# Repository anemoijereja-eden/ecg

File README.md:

E.D.E.N.Tech Open Source Hardware health telemetry system
This project aims to bring the features of medical grade wireless telemetry systems to the people, making them vastly more compact and lowering costs significantly.
Where the average medical grade device that does what this unit can costs hundreds of dollars and only supports proprietary EMR systems, this device uses commodity parts and is intended to connect to an open source telemetry system based on InfluxDB.

Current work completed:
- Signal acquisition using an esp32-s3
- Off device signal processing
- first revision PCB design

To Do:
- Move signal processing onto the device itself
- enable device to report data over the network
- finish PCB designs and create the actual device
- create software solution for processing telemetry data on a recieving server
- Look into other telemetry to integrate

Potential ideas:
- non-invasive blood pressure monitor built more compact than ever before using a PCB motor, integrated cycloidal drive, and a membrane pump to create the full system at a pcb scale.
- integration with implanted sensors via nfc

Tech Stack:
The system is based around the AD8232 as an analog frontend, connected to an ESP32-S3 microcontroller to create a low cost platform using parts that are already widely used and accepted in open hardware.
This repository contains an esp32 firmware, a kicad project under the "PCB" subdirectory, and the prototype off-device processing scripts in "plotter.py"

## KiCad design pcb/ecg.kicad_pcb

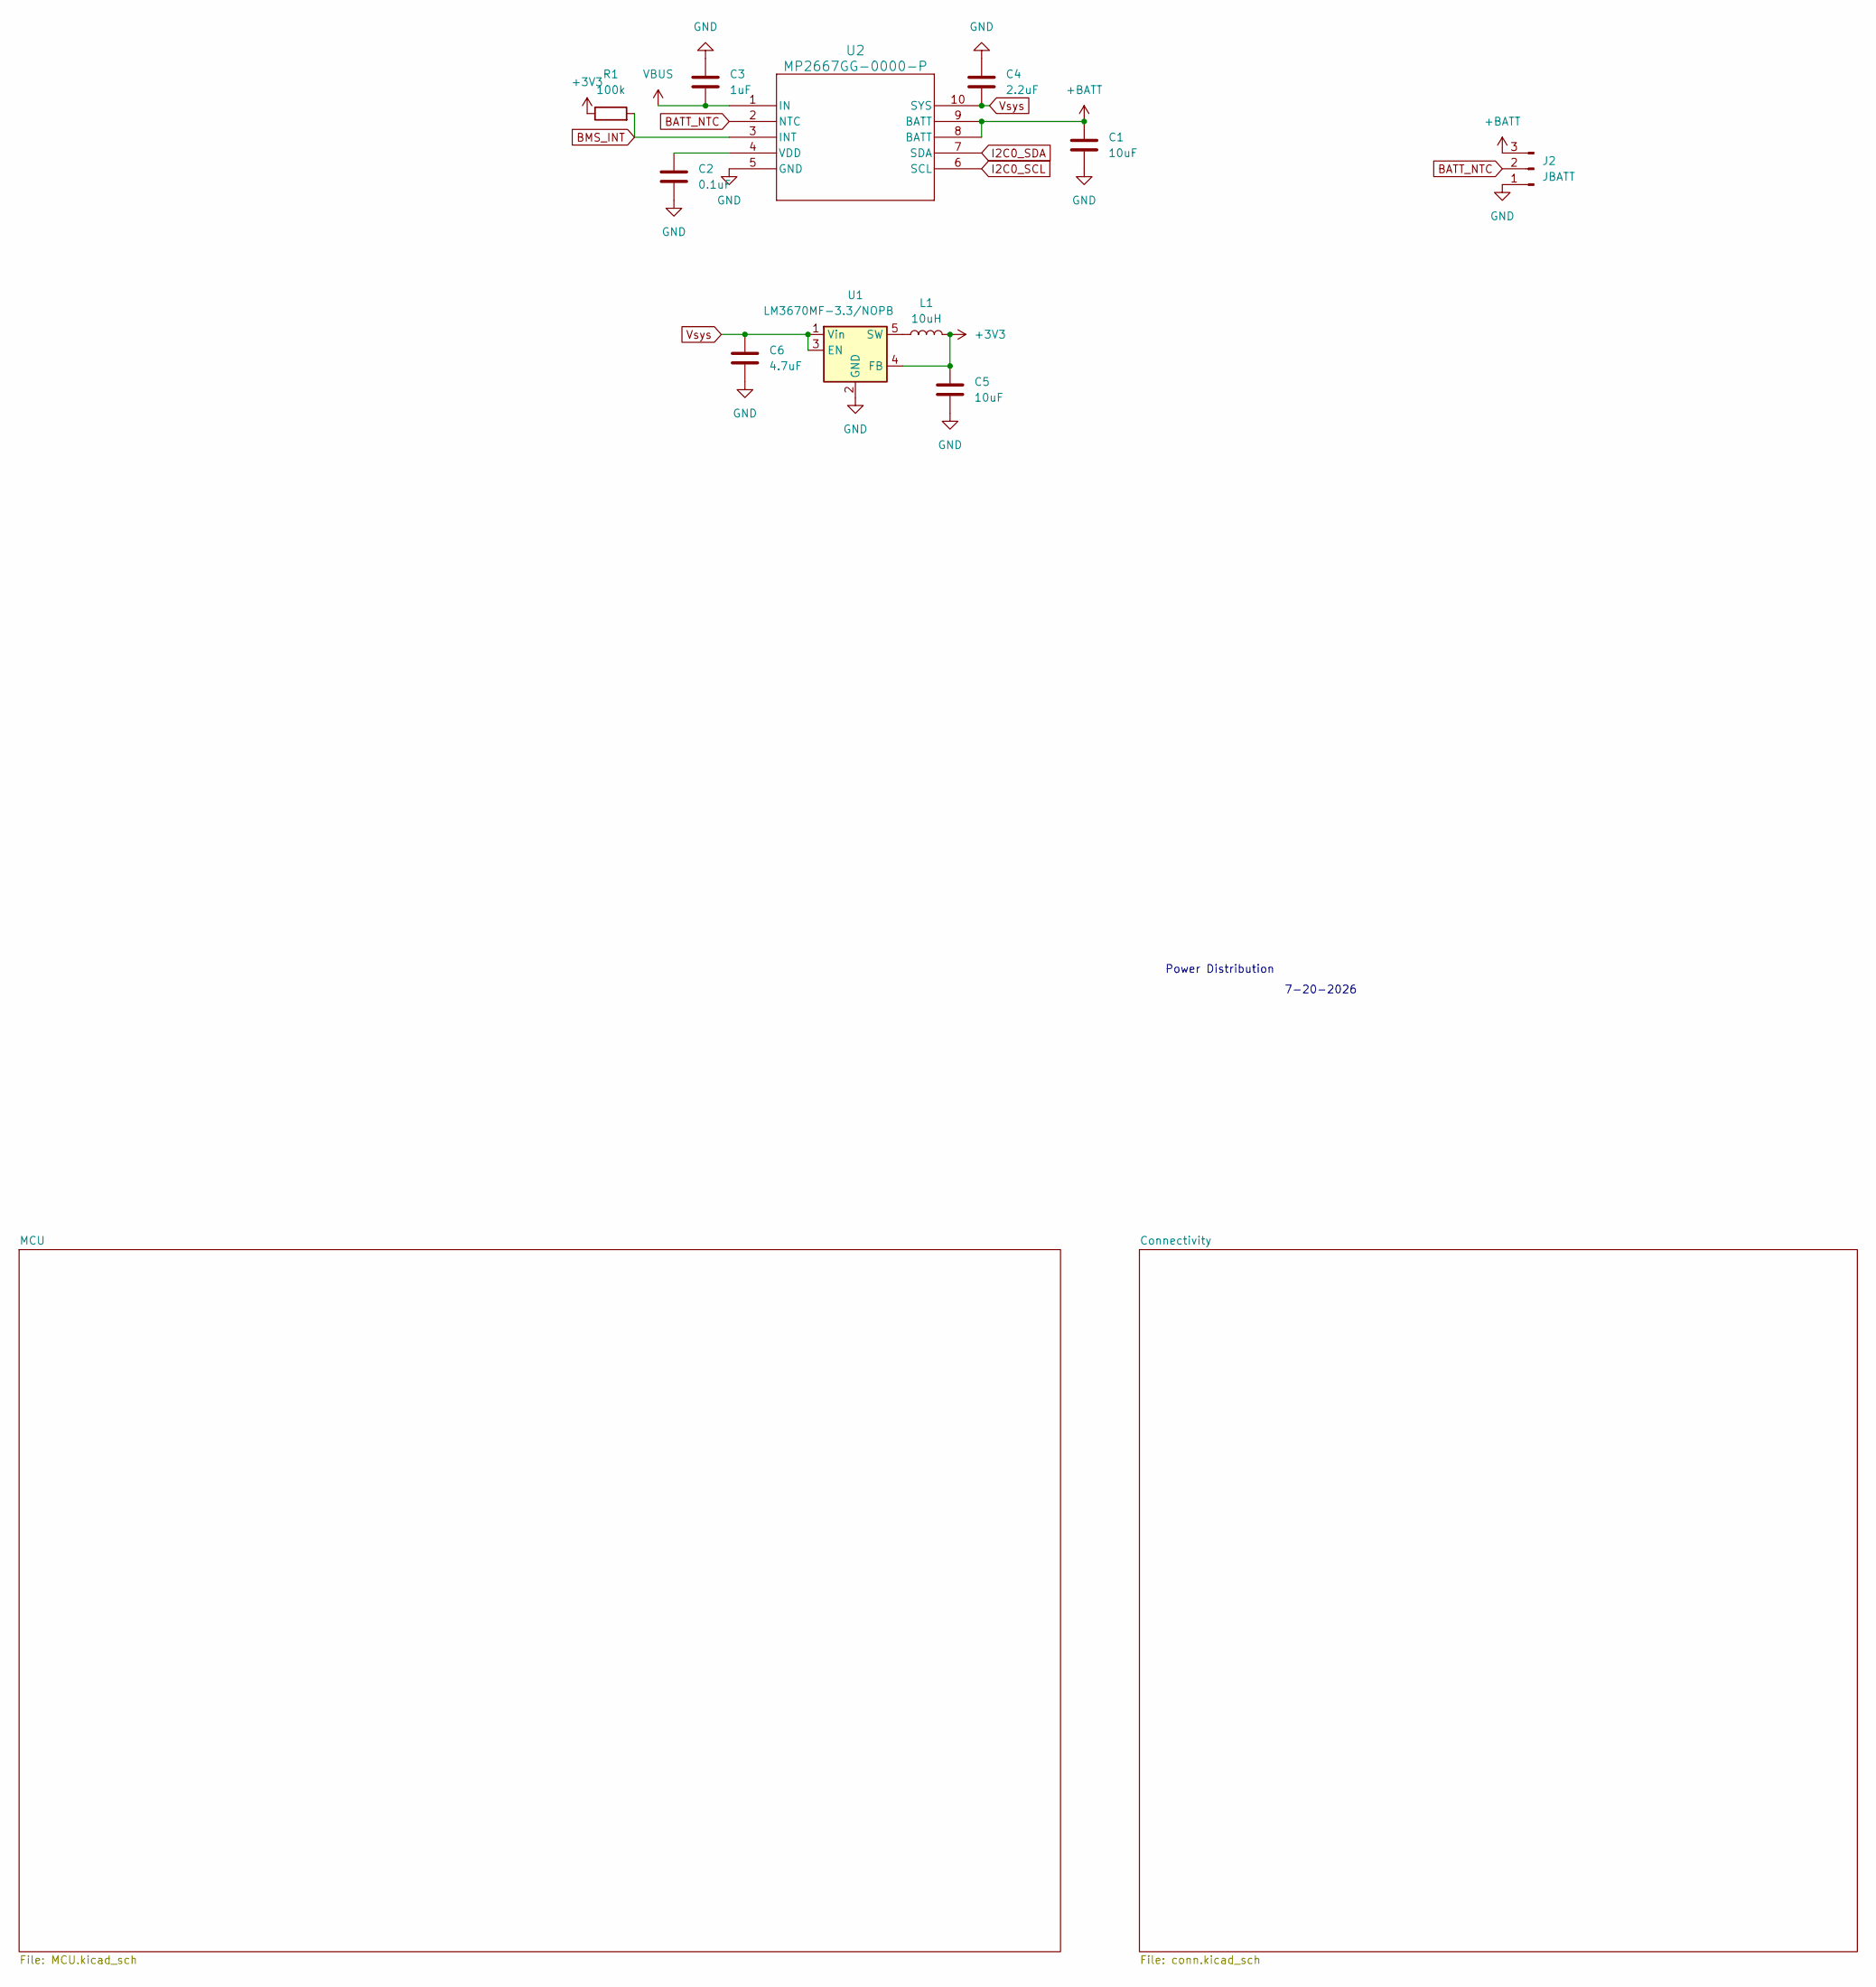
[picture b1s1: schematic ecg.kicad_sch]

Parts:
C1, C5: 10uF; C_0805_2012Metric_Pad1.18x1.45mm_HandSolder
C2: 0.1uF; C_0603_1608Metric_Pad1.08x0.95mm_HandSolder
C3: 1uF; C_0603_1608Metric_Pad1.08x0.95mm_HandSolder
C4: 2.2uF; C_0603_1608Metric_Pad1.08x0.95mm_HandSolder
C6: 4.7uF; C_0805_2012Metric_Pad1.18x1.45mm_HandSolder
J2: JBATT; PinHeader_1x03_P2.54mm_Horizontal
L1: 10uH; L_1210_3225Metric_Pad1.42x2.65mm_HandSolder
R1: 100k; R_0603_1608Metric_Pad0.98x0.95mm_HandSolder
U1: LM3670MF-3.3/NOPB; TSOT-23-5
U2: MP2667GG-0000-P; QFN-10_2MMx2MM_MNP

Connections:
+3V3: C5.1, L1.2, R1.1, U1.4 (FB); also elsewhere on the board
+BATT: C1.1, J2.3, U2.8 (BATT), U2.9 (BATT)
BATT_NTC: J2.2, U2.2 (NTC)
BMS_INT: R1.2, U2.3 (INT); also elsewhere on the board
GND: C1.2, C2.2, C3.1, C4.1, C5.2, C6.2, J2.1, U1.2 (GND), U2.5 (GND); also elsewhere on the board
I2C0_SCL: U2.6 (SCL); also elsewhere on the board
I2C0_SDA: U2.7 (SDA); also elsewhere on the board
unnamed: L1.1, U1.5 (SW)
unnamed: C2.1, U2.4 (VDD)
VBUS: C3.2, U2.1 (IN); also elsewhere on the board
Vsys: C4.2, C6.1, U1.1 (Vin), U1.3 (EN), U2.10 (SYS)

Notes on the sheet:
Power Distribution
7-20-2026

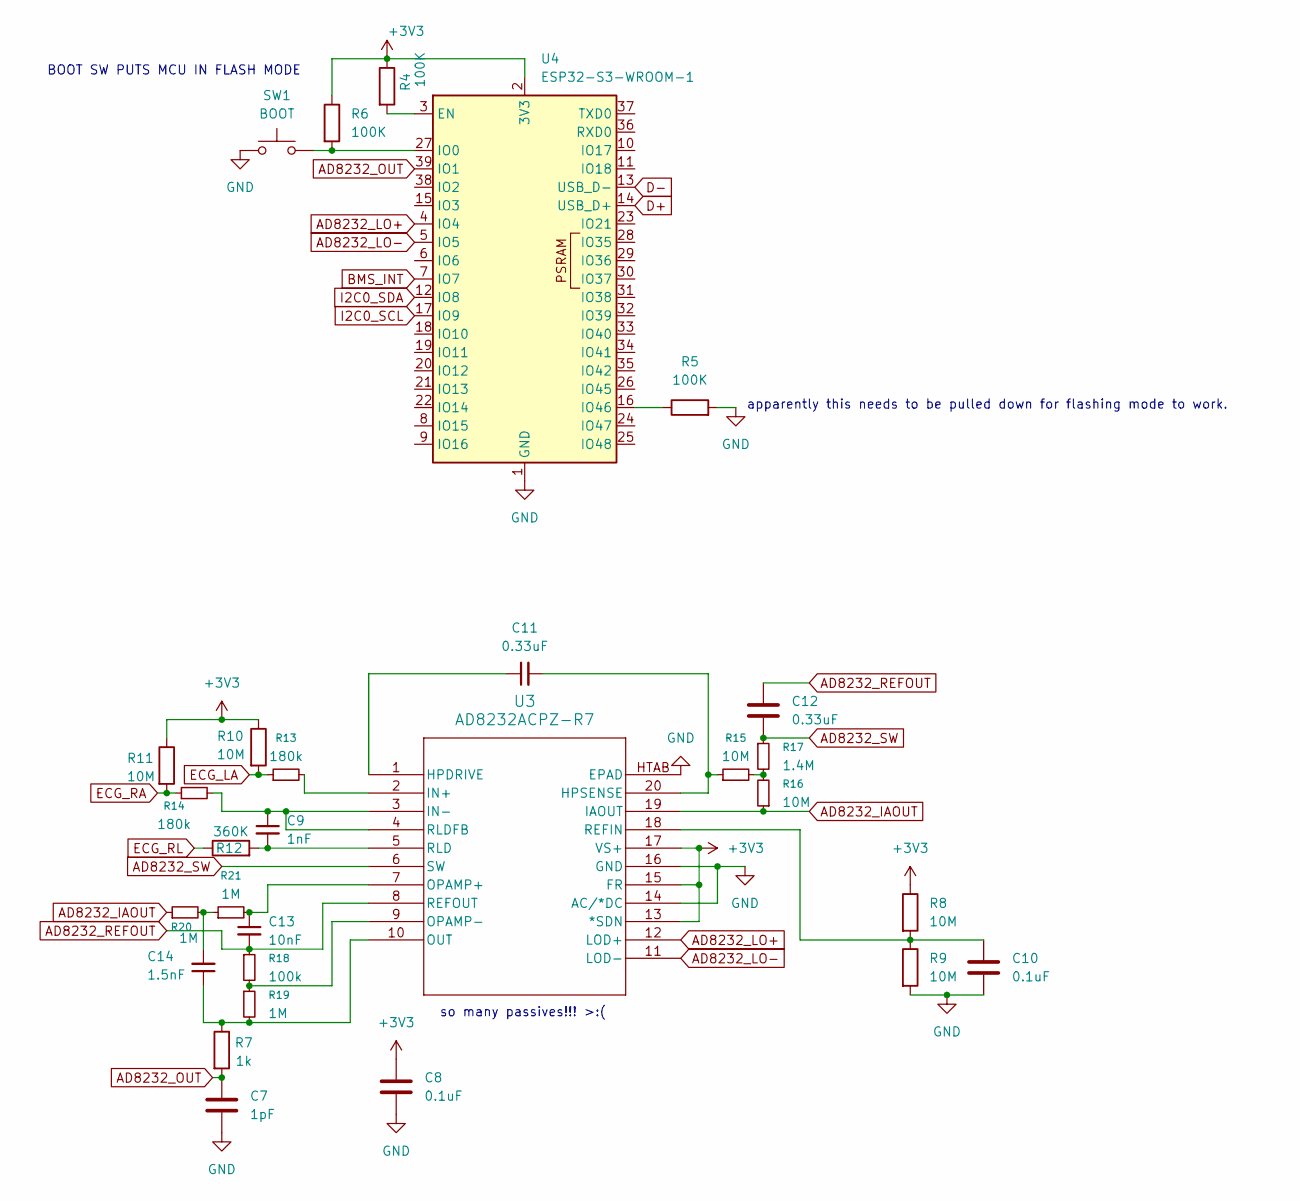
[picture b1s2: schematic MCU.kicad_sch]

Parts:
C7: 1pF; C_0603_1608Metric_Pad1.08x0.95mm_HandSolder
C8, C10: 0.1uF; C_0603_1608Metric_Pad1.08x0.95mm_HandSolder
C9: 1nF; C_0603_1608Metric_Pad1.08x0.95mm_HandSolder
C11, C12: 0.33uF; C_0603_1608Metric_Pad1.08x0.95mm_HandSolder
C13: 10nF; C_0603_1608Metric_Pad1.08x0.95mm_HandSolder
C14: 1.5nF; C_0603_1608Metric_Pad1.08x0.95mm_HandSolder
R4, R5, R6: 100K; R_0603_1608Metric_Pad0.98x0.95mm_HandSolder
R7: 1k; R_0603_1608Metric_Pad0.98x0.95mm_HandSolder
R8, R9, R10, R11, R15, R16: 10M; R_0603_1608Metric_Pad0.98x0.95mm_HandSolder
R12: 360K; R_0603_1608Metric_Pad0.98x0.95mm_HandSolder
R13, R14: 180k; R_0603_1608Metric_Pad0.98x0.95mm_HandSolder
R17: 1.4M; R_0603_1608Metric_Pad0.98x0.95mm_HandSolder
R18: 100k; R_0603_1608Metric_Pad0.98x0.95mm_HandSolder
R19, R20, R21: 1M; R_0603_1608Metric_Pad0.98x0.95mm_HandSolder
SW1: BOOT; SW_Push_1P1T_NO_CK_KMR2
U3: AD8232ACPZ-R7; CP_20_10_ADI
U4: ESP32-S3-WROOM-1

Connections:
+3V3: C8.1, R4.1, R6.1, R8.1, R10.1, R11.1, U3.13 (*SDN), U3.15 (FR), U3.17 (VS+), U4.2 (3V3); also elsewhere on the board
AD8232_IAOUT: R16.1, R20.1, U3.19 (IAOUT)
AD8232_LO+: U3.12 (LOD+), U4.4 (IO4)
AD8232_LO-: U3.11 (LOD-), U4.5 (IO5)
AD8232_OUT: C7.1, R7.2, U4.39 (IO1)
AD8232_REFOUT: C12.1, C13.2, R18.1, U3.8 (REFOUT)
AD8232_SW: C12.2, R17.1, U3.6 (SW)
BMS_INT: U4.7 (IO7); also elsewhere on the board
D+: U4.14 (USB_D+); also elsewhere on the board
D-: U4.13 (USB_D-); also elsewhere on the board
ECG_LA: R10.2, R13.1; also elsewhere on the board
ECG_RA: R11.2, R14.1; also elsewhere on the board
ECG_RL: R12.1; also elsewhere on the board
GND: C7.2, C8.2, C10.2, R5.2, R9.2, SW1.1, U3.14 (AC/*DC), U3.16 (GND), U3.HTAB (EPAD), U4.1 (GND), U4.40 (GND), U4.41 (GND); also elsewhere on the board
I2C0_SCL: U4.17 (IO9); also elsewhere on the board
I2C0_SDA: U4.12 (IO8); also elsewhere on the board
unnamed: C14.2, R20.2, R21.1
unnamed: R15.2, R16.2, R17.2
unnamed: C11.1, U3.1 (HPDRIVE)
unnamed: C11.2, R15.1, U3.20 (HPSENSE)
unnamed: R13.2, U3.2 (IN+)
unnamed: C9.1, R14.2, U3.3 (IN-), U3.4 (RLDFB)
unnamed: C13.1, R21.2, U3.7 (OPAMP+)
unnamed: R18.2, R19.1, U3.9 (OPAMP-)
unnamed: C14.1, R7.1, R19.2, U3.10 (OUT)
unnamed: C10.1, R8.2, R9.1, U3.18 (REFIN)
unnamed: C9.2, R12.2, U3.5 (RLD)
unnamed: R4.2, U4.3 (EN)
unnamed: R6.2, SW1.2, U4.27 (IO0)
unnamed: R5.1, U4.16 (IO46)

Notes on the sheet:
apparently this needs to be pulled down for flashing mode to work.
so many passives!!! >:(
BOOT SW PUTS MCU IN FLASH MODE

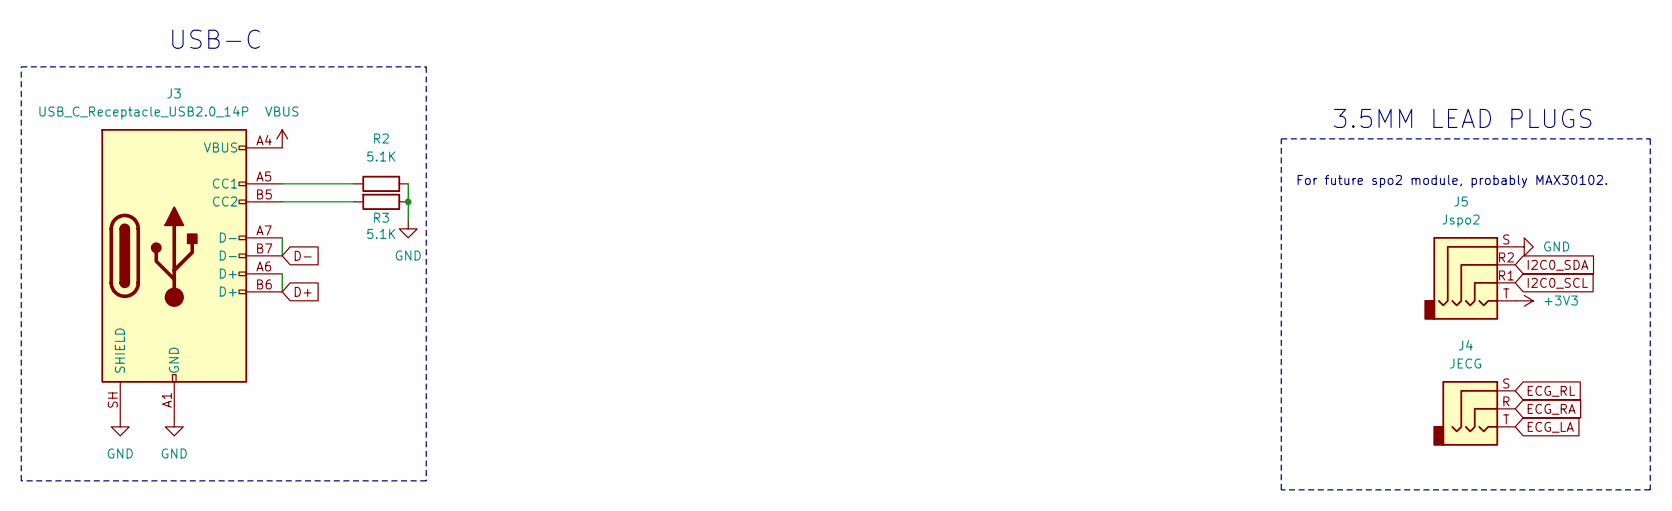
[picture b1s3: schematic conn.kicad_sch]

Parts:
J3: USB_C_Receptacle_USB2.0_14P; USB_C_Receptacle_HCTL_HC-TYPE-C-16P-01A
J4: JECG; Jack_3.5mm_CUI_SJ-3523-SMT_Horizontal
J5: Jspo2; Jack_3.5mm_CUI_SJ-3524-SMT_Horizontal
R2, R3: 5.1K; R_0603_1608Metric_Pad0.98x0.95mm_HandSolder

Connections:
+3V3: J5.T; also elsewhere on the board
D+: J3.A6 (D+), J3.B6 (D+); also elsewhere on the board
D-: J3.A7 (D-), J3.B7 (D-); also elsewhere on the board
ECG_LA: J4.T; also elsewhere on the board
ECG_RA: J4.R; also elsewhere on the board
ECG_RL: J4.S; also elsewhere on the board
GND: J3.A1 (GND), J3.A12 (GND), J3.B1 (GND), J3.B12 (GND), J3.SH (SHIELD), J5.S, R2.2, R3.1; also elsewhere on the board
unnamed: J3.A5 (CC1), R2.1
unnamed: J3.B5 (CC2), R3.2
VBUS: J3.A4 (VBUS), J3.A9 (VBUS), J3.B4 (VBUS), J3.B9 (VBUS); also elsewhere on the board

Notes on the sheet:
For future spo2 module, probably MAX30102.
3.5MM LEAD PLUGS
USB-C

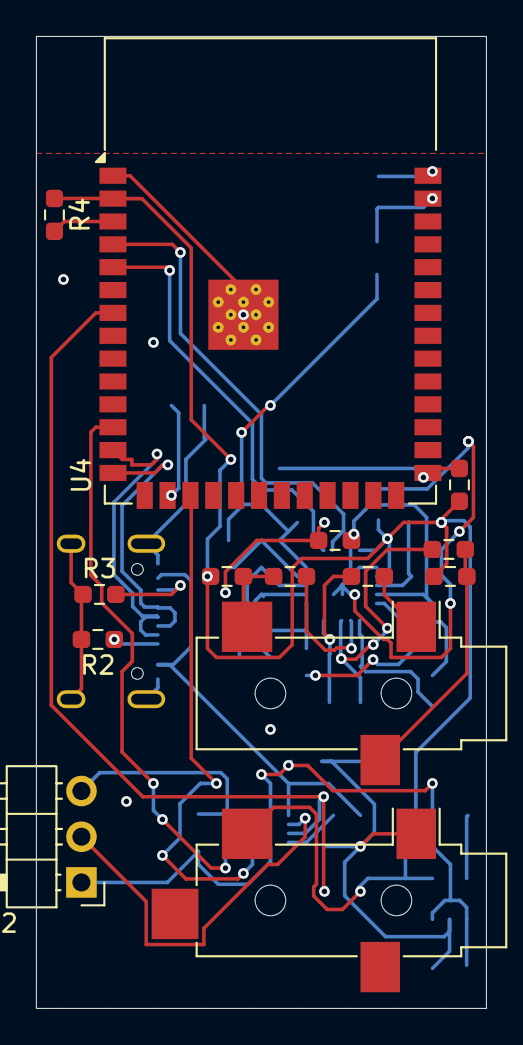
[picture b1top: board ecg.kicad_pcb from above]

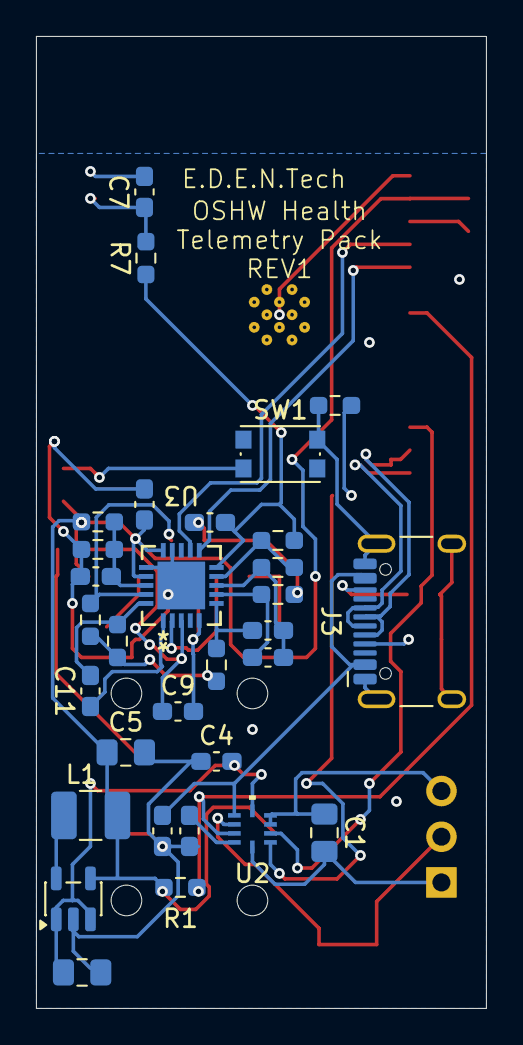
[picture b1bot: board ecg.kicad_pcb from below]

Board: 2 copper layers, 25.0 x 54.0 mm, 45 parts (31 on the bottom side), 38 nets.
